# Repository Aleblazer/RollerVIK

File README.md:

# RollerVIK
3D printable roller encoders in VIK format.

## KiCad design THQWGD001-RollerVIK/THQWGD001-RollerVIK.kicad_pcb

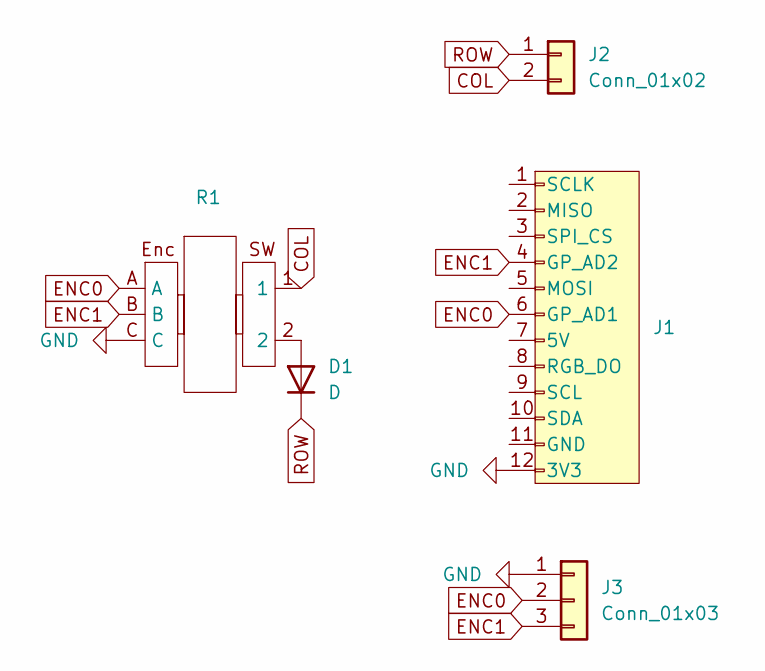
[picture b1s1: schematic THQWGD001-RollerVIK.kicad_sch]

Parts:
D1: D; D_SOD-123
J1: vik-module-connector; vik-module-connector-horizontal
J2: Conn_01x02; PinHeader_1x02_P2.00mm_Vertical
J3: Conn_01x03; PinHeader_1x03_P2.00mm_Vertical
R1: THQWGD001C [4pin] #1

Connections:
COL: J2.2, R1.1
ENC0: J1.6 (GP_AD1), J3.2, R1.A
ENC1: J1.4 (GP_AD2), J3.3, R1.B
GND: J1.12 (3V3), J3.1, R1.C
unnamed: D1.2 (A), R1.2
ROW: D1.1 (K), J2.1

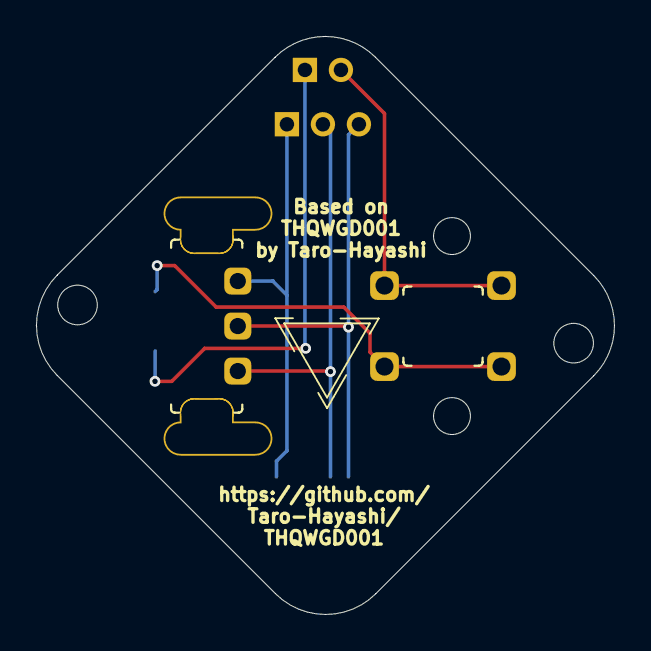
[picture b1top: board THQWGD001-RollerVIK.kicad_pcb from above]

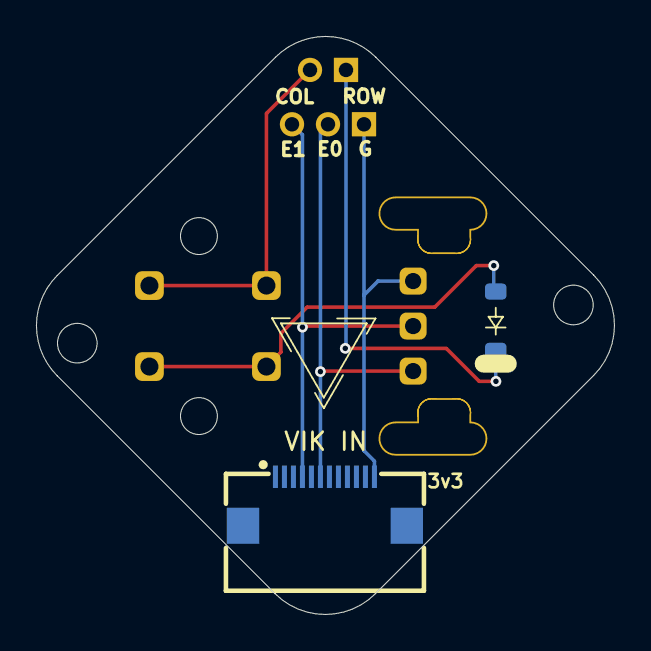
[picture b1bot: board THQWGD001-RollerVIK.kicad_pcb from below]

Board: 2 copper layers, 32.1 x 32.1 mm, 5 parts (2 on the bottom side), 6 nets.

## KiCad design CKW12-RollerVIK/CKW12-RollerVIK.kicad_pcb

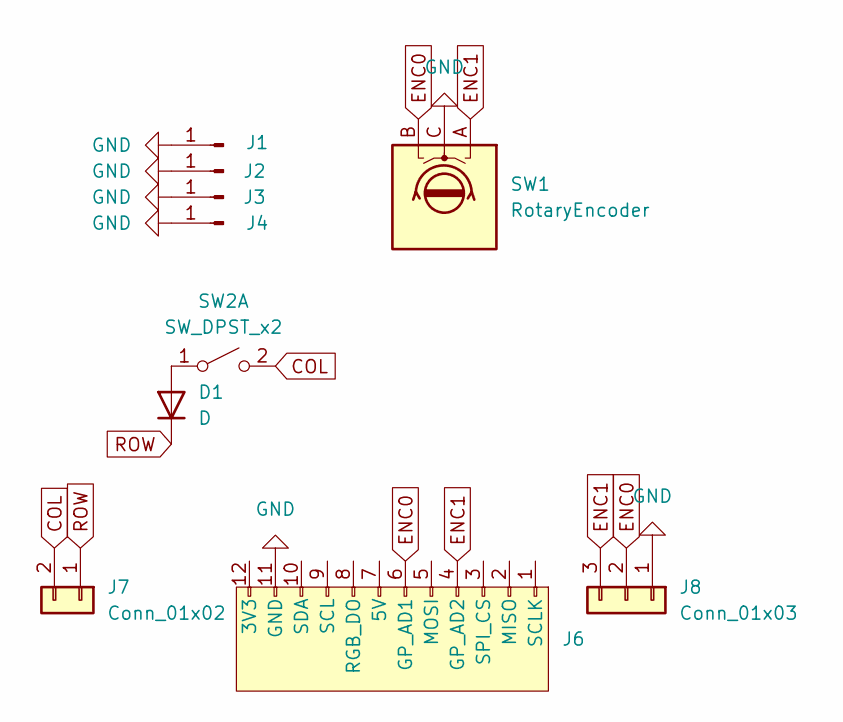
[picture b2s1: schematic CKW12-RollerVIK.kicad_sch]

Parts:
D1: D; D_SOD-128
J1, J2, J3, J4: Conn_01x01_Pin; my_mount_hole_M2_pad
J6: vik-module-connector; vik-module-connector-horizontal
J7: Conn_01x02; PinHeader_1x02_P2.00mm_Vertical
J8: Conn_01x03; PinHeader_1x03_P2.00mm_Vertical
SW1: RotaryEncoder; EC05E1220202
SW2: SW_DPST_x2; SKQYACE010

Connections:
COL: J7.2, SW2.2 (B)
ENC0: J6.6 (GP_AD1), J8.2, SW1.B
ENC1: J6.4 (GP_AD2), J8.3, SW1.A
GND: J1.1, J2.1, J3.1, J4.1, J6.11 (GND), J8.1, SW1.C
unnamed: D1.2 (A), SW2.1 (A)
ROW: D1.1 (K), J7.1

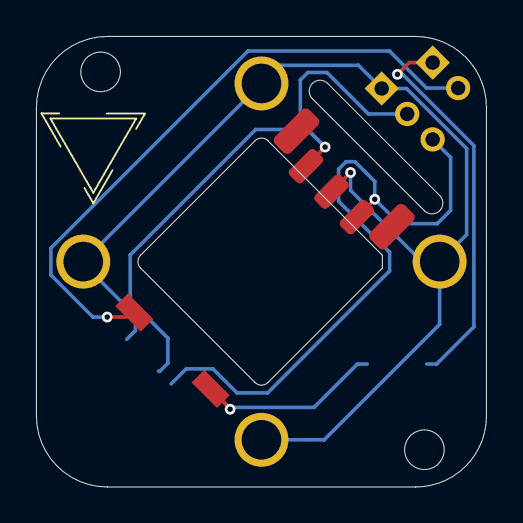
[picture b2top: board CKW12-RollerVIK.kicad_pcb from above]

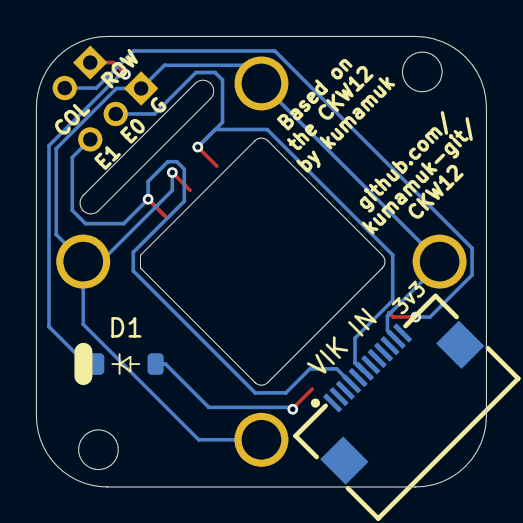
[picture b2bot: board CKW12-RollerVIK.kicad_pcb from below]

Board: 2 copper layers, 25.0 x 25.0 mm, 10 parts (2 on the bottom side), 6 nets.

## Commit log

2025-08-03 Adding CKW12 version
2025-08-04 Added THQWGD001
2025-08-05 Adjusted the diode placement
